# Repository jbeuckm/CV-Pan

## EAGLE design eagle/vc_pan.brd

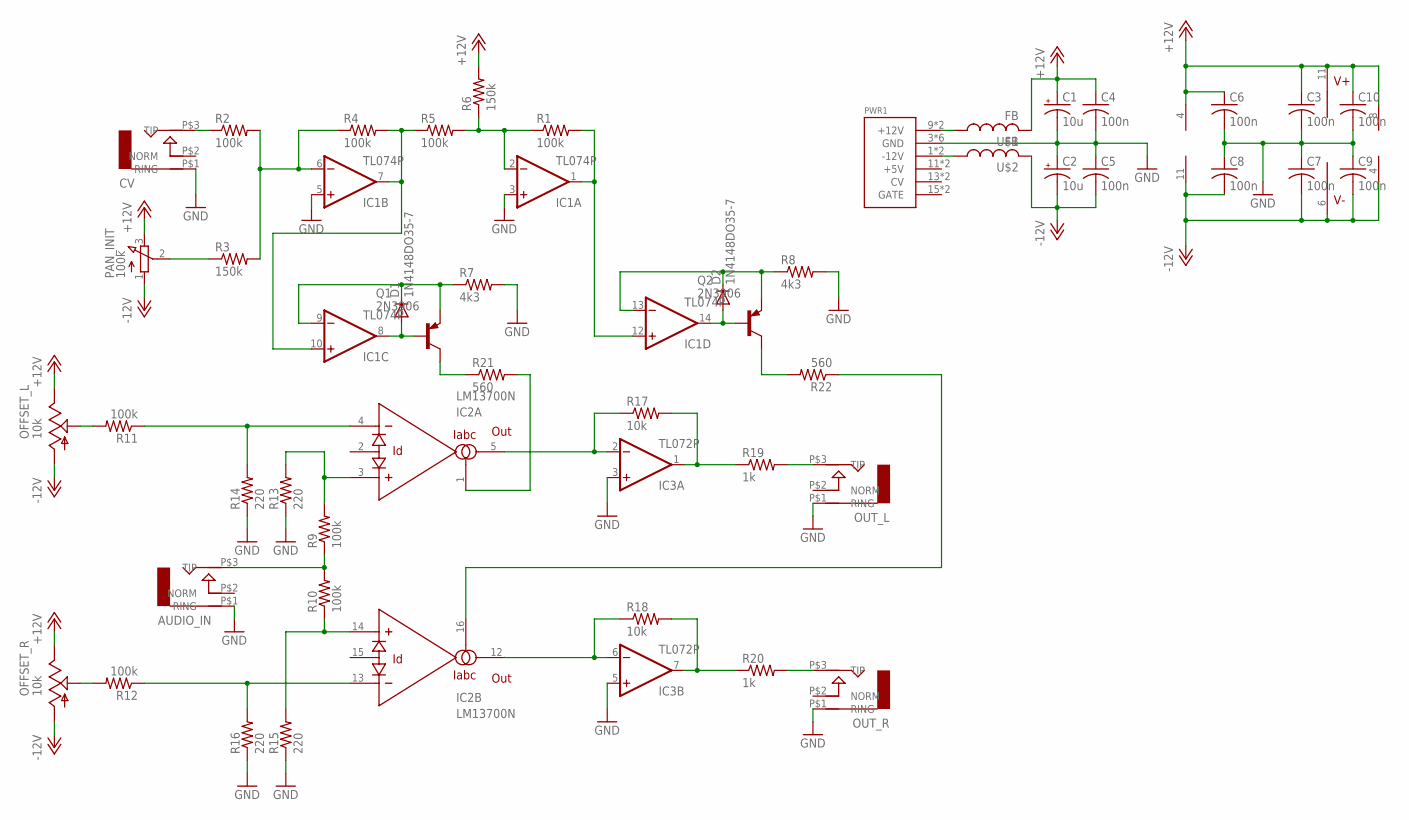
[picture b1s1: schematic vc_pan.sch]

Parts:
AUDIO_IN: AUDIO-JACK; ERTHENVAR-JACK-90DEG
C1, C2: 10u; B45181A
C3, C4, C5, C6, C7, C8, C9, C10: 100n; C050-024X044
CV: AUDIO-JACK; ERTHENVAR-JACK-90DEG
D1, D2: 1N4148DO35-7; DO35-7
IC1: TL074P; DIL14
IC2: LM13700N; DIL16
IC3: TL072P; DIL08
OFFSET_L: 10k; B64Y
OFFSET_R: 10k; B64Y
OUT_L: AUDIO-JACK; ERTHENVAR-JACK-90DEG
OUT_R: AUDIO-JACK; ERTHENVAR-JACK-90DEG
PAN_INIT: 100k; 3RP/1610N
PWR1: POWER; POWER_16
Q1, Q2: 2N3906; TO92
R1, R2, R4, R5, R9, R10, R11, R12: 100k; 0207/10
R3, R6: 150k; 0207/10
R7, R8: 4k3; 0207/10
R13, R14, R15, R16: 220; 0207/10
R17, R18: 10k; 0207/10
R19, R20: 1k; 0207/10
R21, R22: 560; 0207/10
U$1, U$2: FB

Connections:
+12V: C1.+, C3.1, C4.1, C6.1, C10.1, IC1.4 (V+), IC2.11 (V+), IC3.8 (V+), OFFSET_L.E, OFFSET_R.E, PAN_INIT.3 (E), R6.2, U$1.P$2 (2)
-12V: C2.-, C5.2, C7.2, C8.2, C9.2, IC1.11 (V-), IC2.6 (V-), IC3.4 (V-), OFFSET_L.A, OFFSET_R.A, PAN_INIT.1 (A), U$2.P$2 (2)
GND: AUDIO_IN.P$1 (RING), C1.-, C2.+, C3.2, C4.2, C5.1, C6.2, C7.1, C8.1, C9.1, C10.2, CV.P$1 (RING), IC1.3 (+IN), IC1.5 (+IN), IC3.3 (+IN), IC3.5 (+IN), OUT_L.P$1 (RING), OUT_R.P$1 (RING), PWR1.3 (GND), PWR1.4 (GND), PWR1.5 (GND), PWR1.6 (GND), PWR1.7 (GND), PWR1.8 (GND), R7.2, R8.2, R13.1, R14.1, R15.1, R16.1
unnamed: PWR1.9 (+12V), PWR1.10 (+12V), U$1.P$1 (1)
unnamed: PWR1.1 (-12V), PWR1.2 (-12V), U$2.P$1 (1)
unnamed: CV.P$3 (TIP), R2.1
unnamed: PAN_INIT.2 (S), R3.1
unnamed: IC1.6 (-IN), R2.2, R3.2, R4.1
unnamed: IC1.7 (OUT), IC1.10 (+IN), R4.2, R5.1
unnamed: IC1.2 (-IN), R1.1, R5.2, R6.1
unnamed: IC1.1 (OUT), IC1.12 (+IN), R1.2
unnamed: D1.A, IC1.8 (OUT), Q1.2 (B)
unnamed: D2.A, IC1.14 (OUT), Q2.2 (B)
unnamed: D1.C, IC1.9 (-IN), Q1.3 (E), R7.1
unnamed: D2.C, IC1.13 (-IN), Q2.3 (E), R8.1
unnamed: AUDIO_IN.P$3 (TIP), R9.1, R10.2
unnamed: IC2.3 (+IN), R9.2, R13.2
unnamed: IC2.14 (+IN), R10.1, R15.2
unnamed: IC2.4 (-IN), R11.1, R14.2
unnamed: IC2.13 (-IN), R12.1, R16.2
unnamed: OFFSET_R.S, R12.2
unnamed: OFFSET_L.S, R11.2
unnamed: IC3.7 (OUT), R18.2, R20.1
unnamed: IC2.5 (OUT), IC3.2 (-IN), R17.1
unnamed: IC2.12 (OUT), IC3.6 (-IN), R18.1
unnamed: IC3.1 (OUT), R17.2, R19.1
unnamed: OUT_L.P$3 (TIP), R19.2
unnamed: OUT_R.P$3 (TIP), R20.2
unnamed: Q2.1 (C), R22.2
unnamed: IC2.16 (IABC), R22.1
unnamed: IC2.1 (IABC), R21.2
unnamed: Q1.1 (C), R21.1

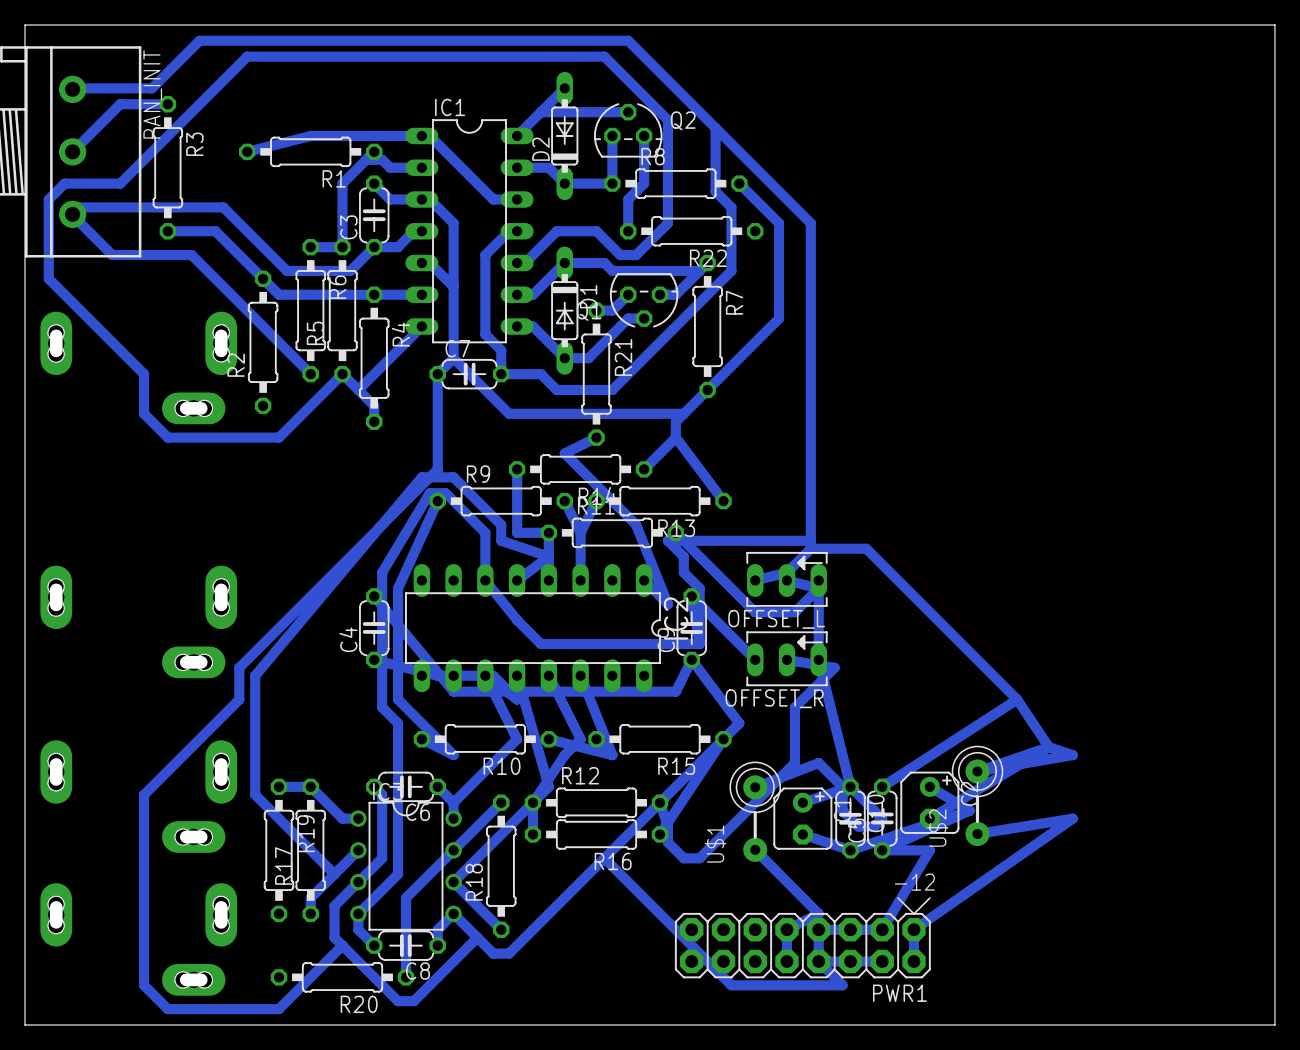
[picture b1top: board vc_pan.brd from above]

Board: 2 copper layers, 100.0 x 80.0 mm, 49 parts (0 on the bottom side), 32 nets.

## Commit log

2016-01-20 schemo
2016-02-16 half rerouted
2016-02-16 85 percentish routed
